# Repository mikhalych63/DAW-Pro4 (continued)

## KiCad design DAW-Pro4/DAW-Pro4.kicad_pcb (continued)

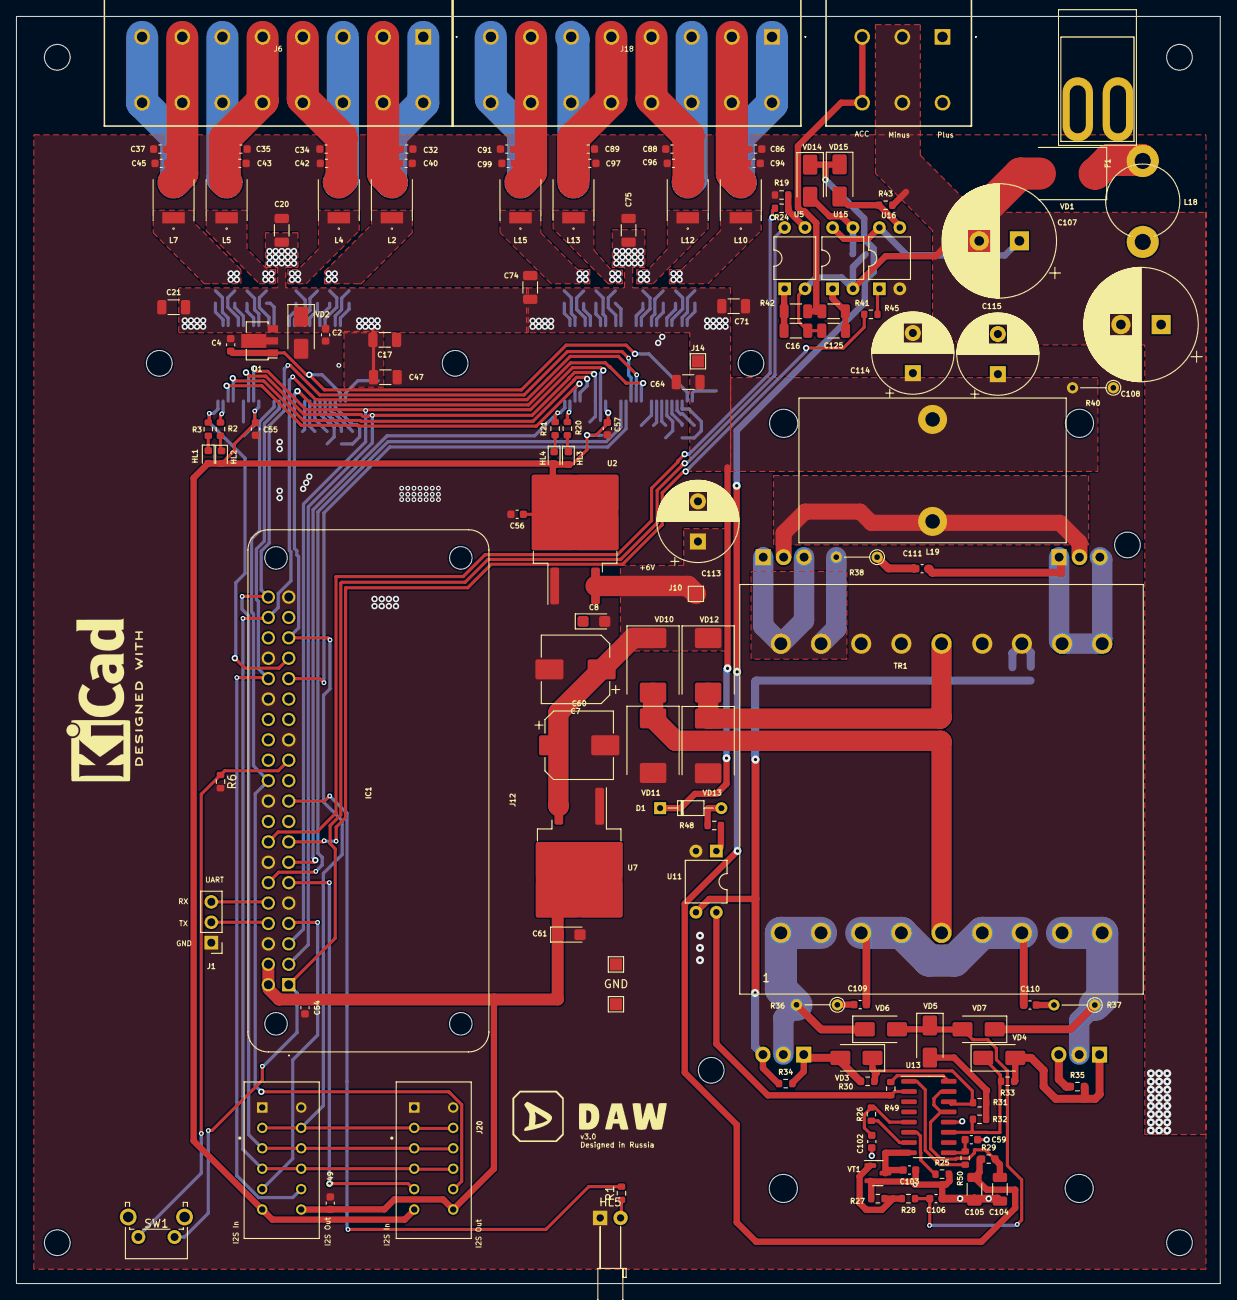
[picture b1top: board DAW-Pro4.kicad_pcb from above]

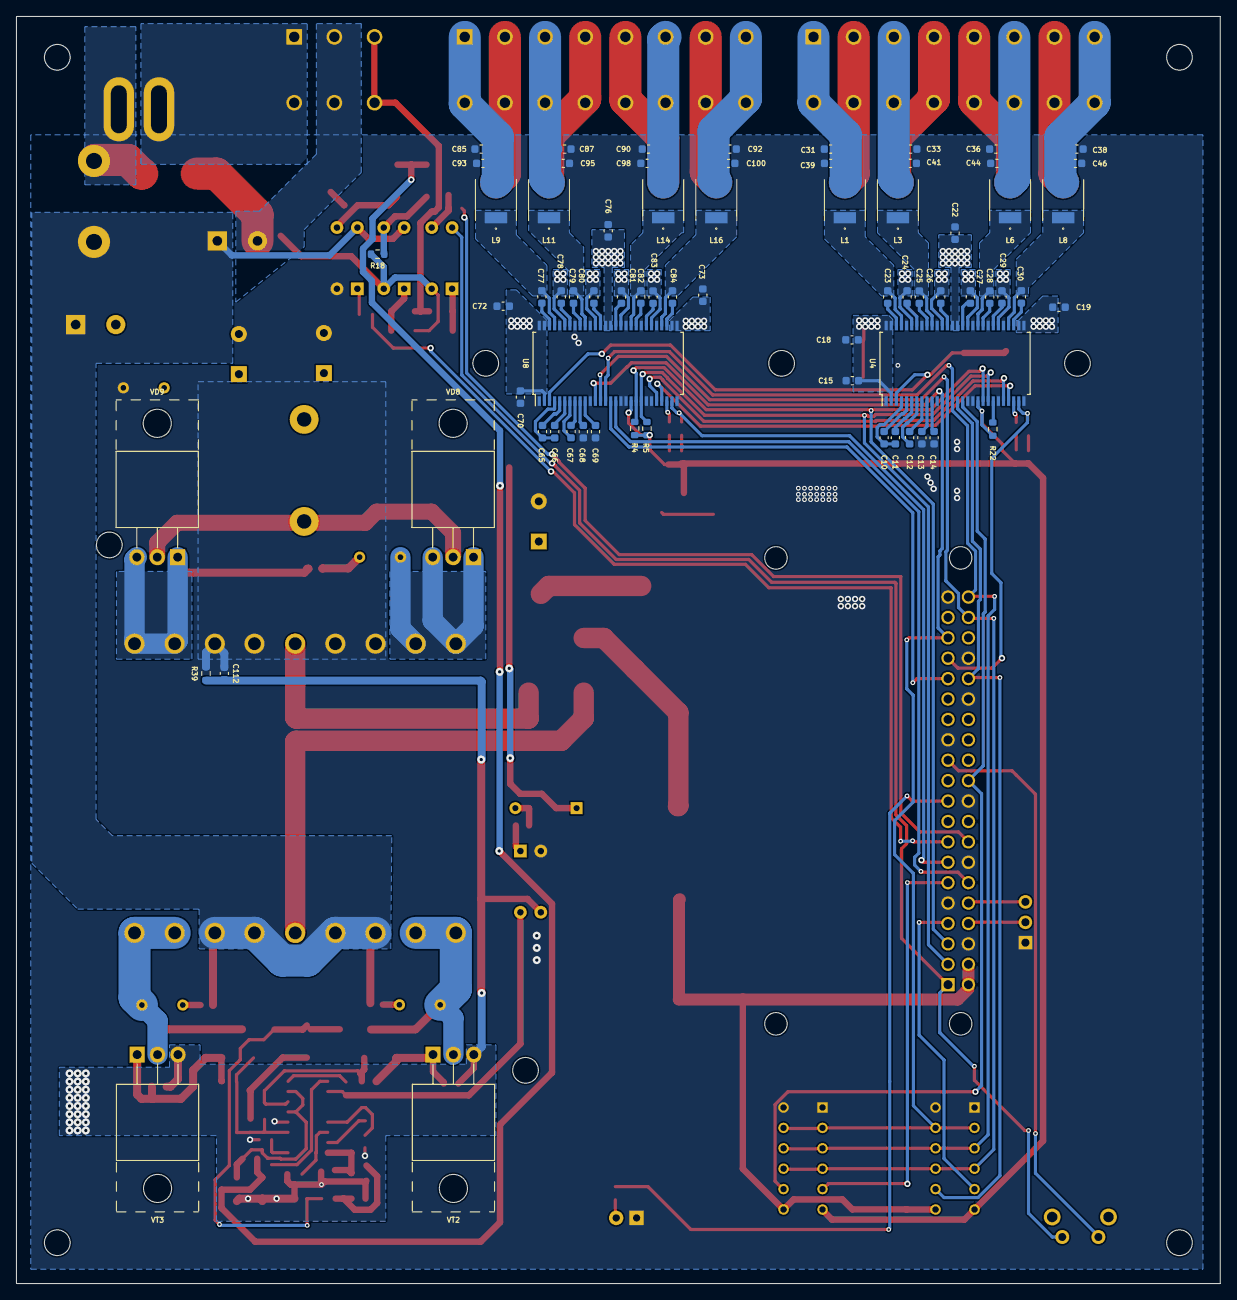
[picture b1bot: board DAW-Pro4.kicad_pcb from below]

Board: 2 copper layers, 149.9 x 157.7 mm, 203 parts (70 on the bottom side), 138 nets.

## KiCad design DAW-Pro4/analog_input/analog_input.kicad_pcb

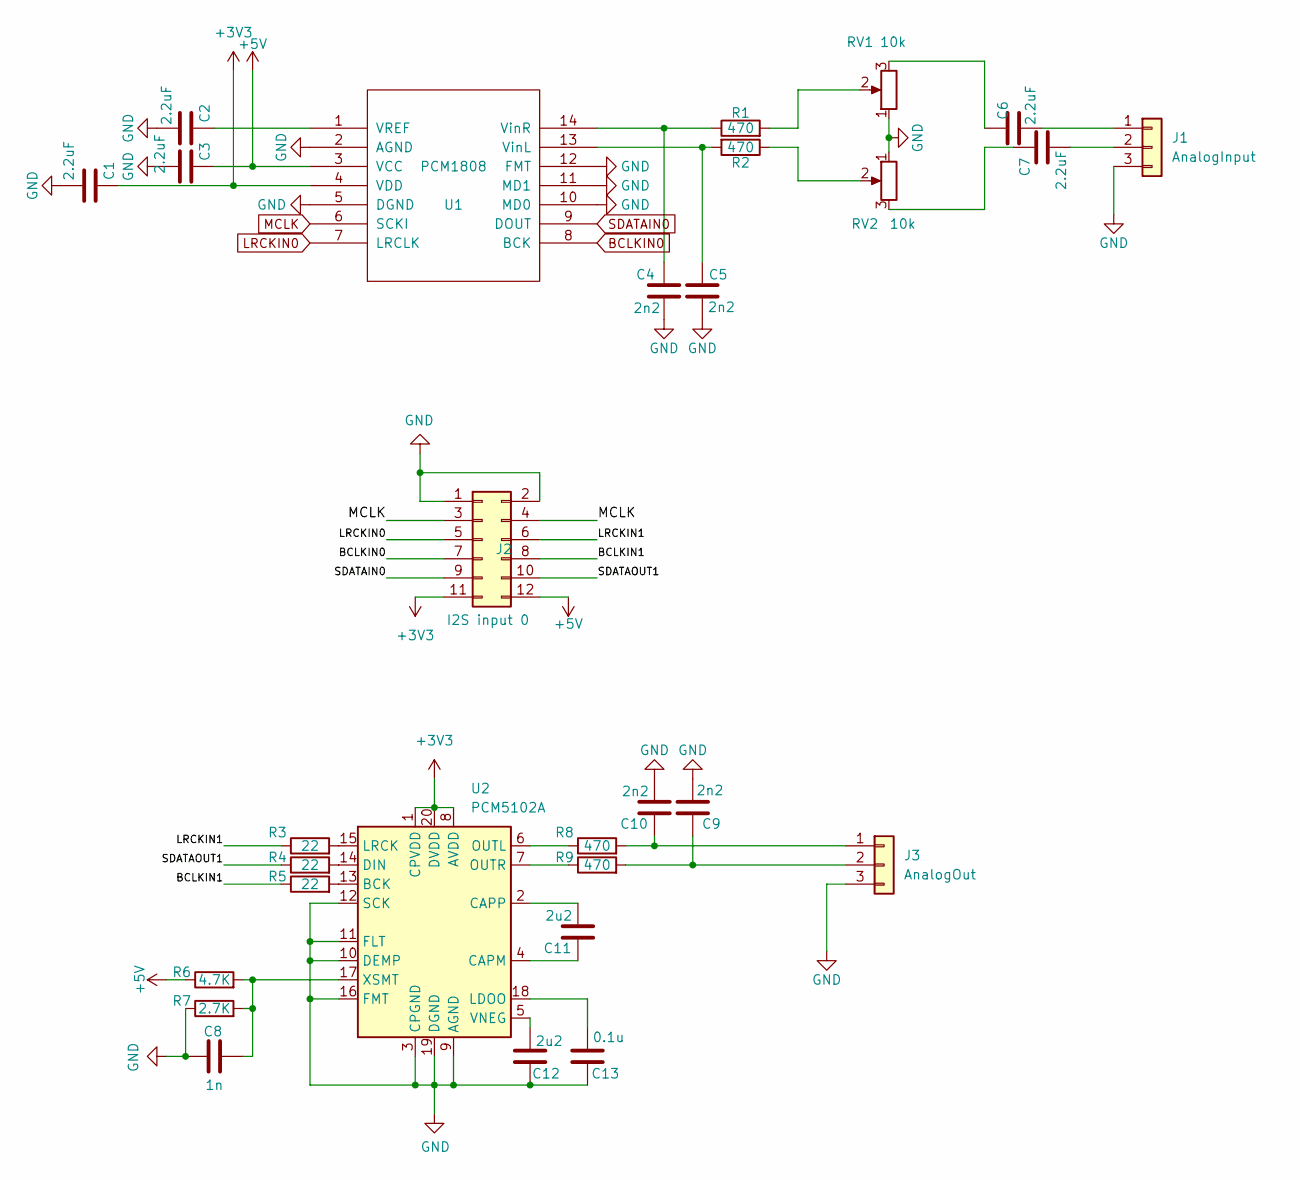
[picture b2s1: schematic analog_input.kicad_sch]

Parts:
C1, C2, C3, C6, C7: 2.2uF; C_0805_2012Metric
C4, C5, C9, C10: 2n2; C_0603_1608Metric
C8: 1n; C_0603_1608Metric
C11, C12: 2u2; C_0603_1608Metric
C13: 0.1u; C_0603_1608Metric
J1: AnalogInput; JST_XH_B3B-XH-A_1x03_P2.50mm_Vertical
J2: Conn_01x06_Male; EDGE-2x6-2.54
J3: AnalogOut; JST_XH_B3B-XH-A_1x03_P2.50mm_Vertical
R1, R2, R8, R9: 470; R_0603_1608Metric
R3, R4, R5: 22; R_0603_1608Metric
R6: 4.7K; R_0603_1608Metric
R7: 2.7K; R_0603_1608Metric
RV1, RV2: 10k; Potentiometer_Bourns_3314G_Vertical
U1: PCM1808; TSSOP-14_4.4x5mm_P0.65mm
U2: PCM5102A; TSSOP-20_4.4x6.5mm_P0.65mm

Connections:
+3V3: C1.1, J2.11, U1.4 (VDD), U2.1 (CPVDD), U2.8 (AVDD), U2.20 (DVDD)
+5V: C3.1, J2.12, R6.1, U1.3 (VCC)
/BCLKIN1: J2.8, R5.1
/LRCKIN1: J2.6, R3.1
/SDATAOUT1: J2.10, R4.1
BCLKIN0: J2.7, U1.8 (BCK)
GND: C1.2, C2.2, C3.2, C4.1, C5.1, C8.2, C9.1, C10.1, C12.2, C13.2, J1.3, J2.1, J2.2, J3.3, R7.1, RV1.1, RV2.1, U1.2 (AGND), U1.5 (DGND), U1.10 (MD0), U1.11 (MD1), U1.12 (FMT), U2.3 (CPGND), U2.9 (AGND), U2.10 (DEMP), U2.11 (FLT), U2.12 (SCK), U2.16 (FMT), U2.19 (DGND)
LRCKIN0: J2.5, U1.7 (LRCLK)
MCLK: J2.3, J2.4, U1.6 (SCKI)
unnamed: C6.2, RV1.3
unnamed: C7.1, RV2.3
unnamed: C6.1, J1.1
unnamed: C7.2, J1.2
unnamed: C10.2, J3.1, R8.2
unnamed: C9.2, J3.2, R9.2
unnamed: R1.2, RV1.2
unnamed: R2.1, RV2.2
unnamed: C2.1, U1.1 (VREF)
unnamed: C5.2, R2.2, U1.13 (VinL)
unnamed: C4.2, R1.1, U1.14 (VinR)
unnamed: R5.2, U2.13 (BCK)
unnamed: C11.2, U2.4 (CAPM)
unnamed: C11.1, U2.2 (CAPP)
unnamed: R4.2, U2.14 (DIN)
unnamed: C13.1, U2.18 (LDOO)
unnamed: R3.2, U2.15 (LRCK)
unnamed: R8.1, U2.6 (OUTL)
unnamed: R9.1, U2.7 (OUTR)
unnamed: C12.1, U2.5 (VNEG)
unnamed: C8.1, R6.2, R7.2, U2.17 (XSMT)
SDATAIN0: J2.9, U1.9 (DOUT)

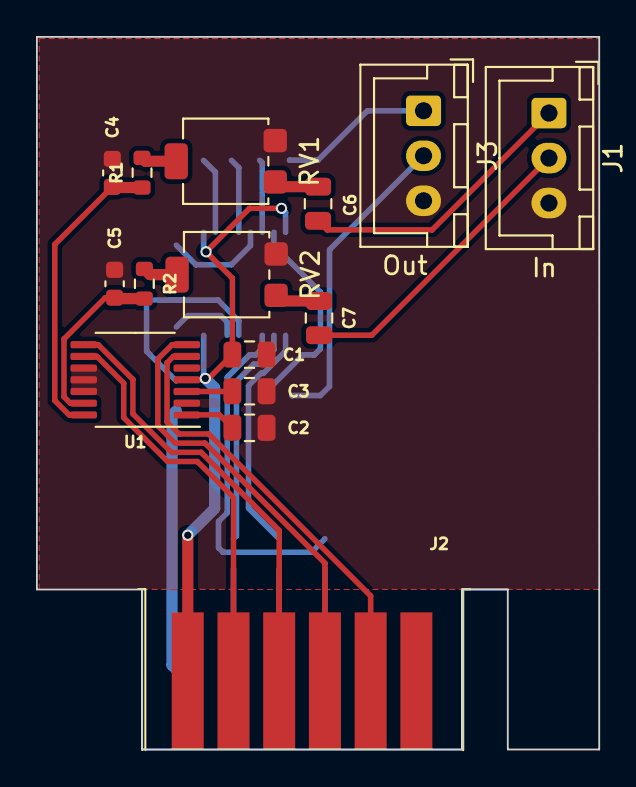
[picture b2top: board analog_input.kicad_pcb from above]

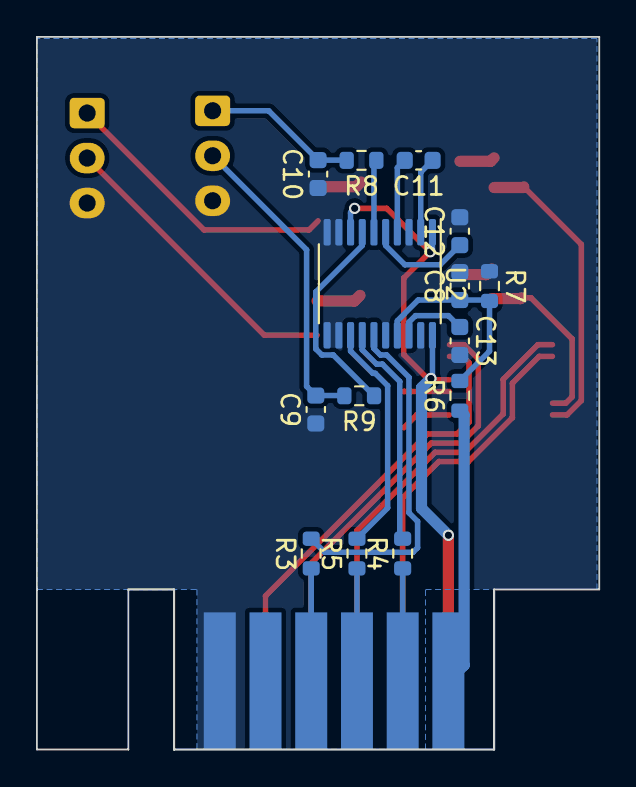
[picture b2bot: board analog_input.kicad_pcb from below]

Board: 2 copper layers, 31.2 x 39.6 mm, 29 parts (14 on the bottom side), 31 nets.

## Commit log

2024-10-08 Main commit
